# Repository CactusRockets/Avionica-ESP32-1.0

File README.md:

A aviônica embarcada foi prototipada e projetada através do software Eagle. Esse projeto inclui as dimensões da placa (PCB), a inclusão dos componentes da aviônica, as relações entre elas e o fornecimento de energia.

Dimensões da placa: 5,6 cm x 12,0 cm

Os materiais incluídos no projeto são:

- 1x PCB
- 1x ESP32 LoRa heltec (V2) + Antena
- 1x MPU6050
- 1X BMP280
- 2x JST de dois pinos (macho e fêmea) (2.54mm)
- 1x Conector microUSB
- 1x Switch (ss12f44g4)
- 1x Módulo SD + Cartão SD
- 1x Pino (PINHD 1X1)
- 2x Baterias de lítio (18650) (3.7V cada)
- 1x Suporte para duas baterias 18650
- Fios de ligação das baterias com o sistema

As trilhas da conexão entre os circuitos foram trilhas de 1mm de largura. A prototipação inclui uma chave de conexão que liga o JST (que se conecta a bateria) ao restante do circuito, para que possa ser feito um acionamento elétrico manual do sistema. Além desses componentes básicos, o projeto da placa inclui também 4x rebites de 2,7mm nas extremidades para fixação da placa.

O CAD está disponível no google Drive da Cactus.

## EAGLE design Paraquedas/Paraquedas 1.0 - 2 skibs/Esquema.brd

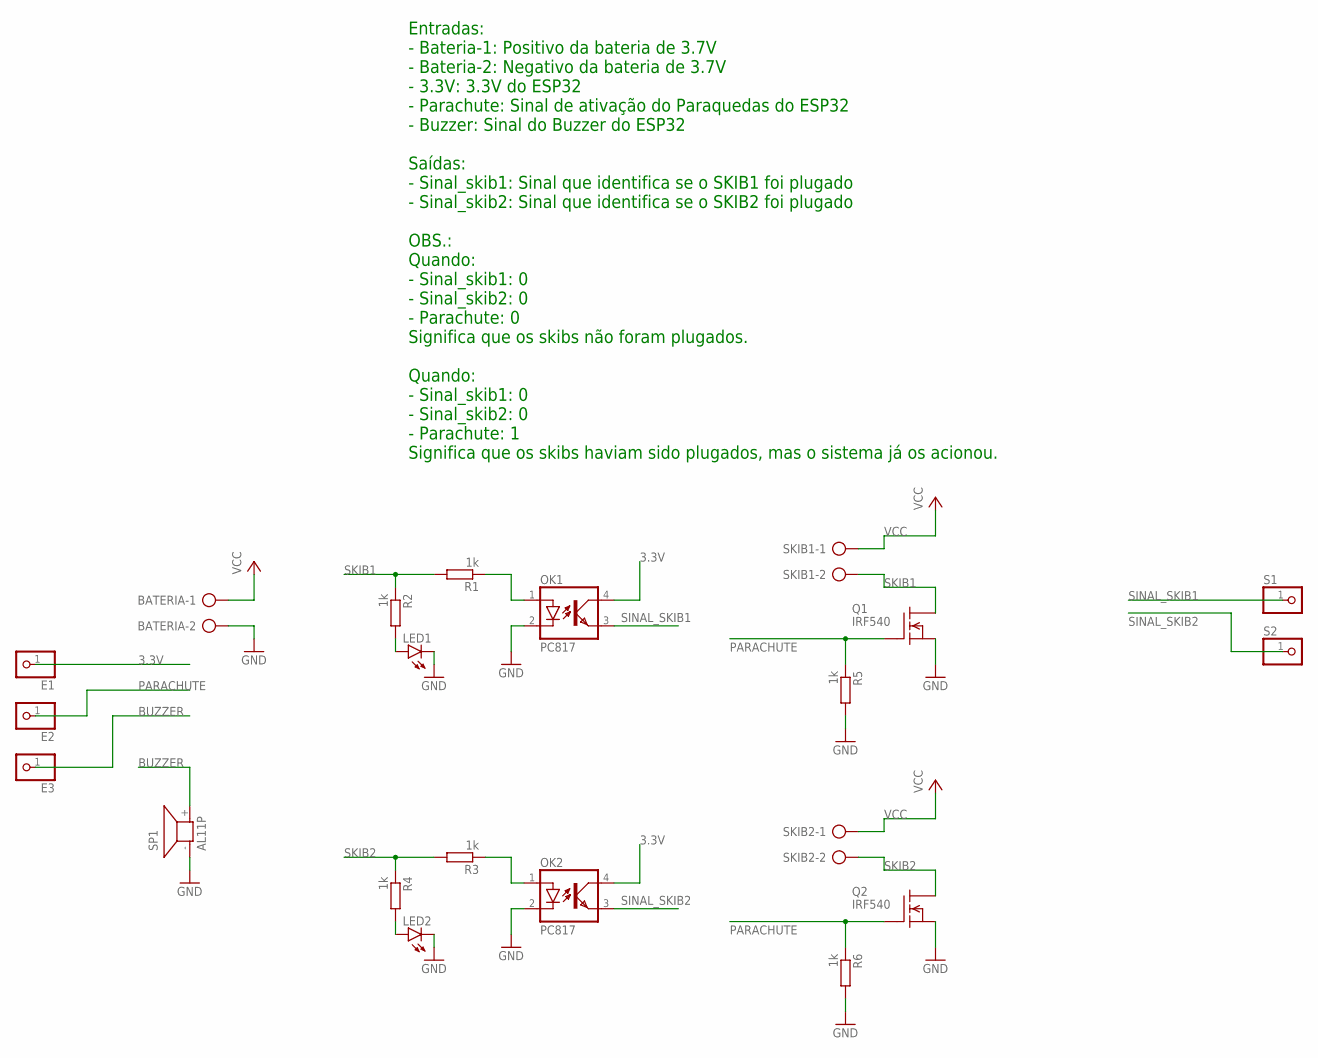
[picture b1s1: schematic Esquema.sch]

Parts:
BATERIA: AK500/2-H
E1, E2, E3: PINHD-1X1; 1X01
LED1, LED2: LED5MM
OK1, OK2: PC817; DIL04
Q1, Q2: IRF540; TO220
R1, R2, R3, R4, R5, R6: 1k; 0207/10
S1, S2: PINHD-1X1; 1X01
SKIB1, SKIB2: AK500/2-H
SP1: AL11P

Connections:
3.3V: E1.1, OK1.4 (COL), OK2.4 (COL)
BUZZER: E3.1, SP1.+ (2)
GND: BATERIA.2, LED1.K (C), LED2.K (C), OK1.2 (C), OK2.2 (C), Q1.3 (S), Q2.3 (S), R5.2, R6.2, SP1.- (1)
unnamed: OK1.1 (A), R1.1
unnamed: OK2.1 (A), R3.1
unnamed: LED2.A, R4.2
unnamed: LED1.A, R2.2
PARACHUTE: E2.1, Q1.1 (G), Q2.1 (G), R5.1, R6.1
SINAL_SKIB1: OK1.3 (EMIT), S1.1
SINAL_SKIB2: OK2.3 (EMIT), S2.1
SKIB1: Q1.2 (D), R1.2, R2.1, SKIB1.2
SKIB2: Q2.2 (D), R3.2, R4.1, SKIB2.2
VCC: BATERIA.1, SKIB1.1, SKIB2.1

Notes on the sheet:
Entradas: - Bateria-1: Positivo da bateria de 3.7V - Bateria-2: Negativo da bateria de 3.7V - 3.3V: 3.3V do ESP32 - Parachute: Sinal de ativação do Paraquedas do ESP32 - Buzzer: Sinal do Buzzer do ESP32 Saídas: - Sinal_skib1: Sinal que identifica se o SKIB1 foi plugado - Sinal_skib2: Sinal que iden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

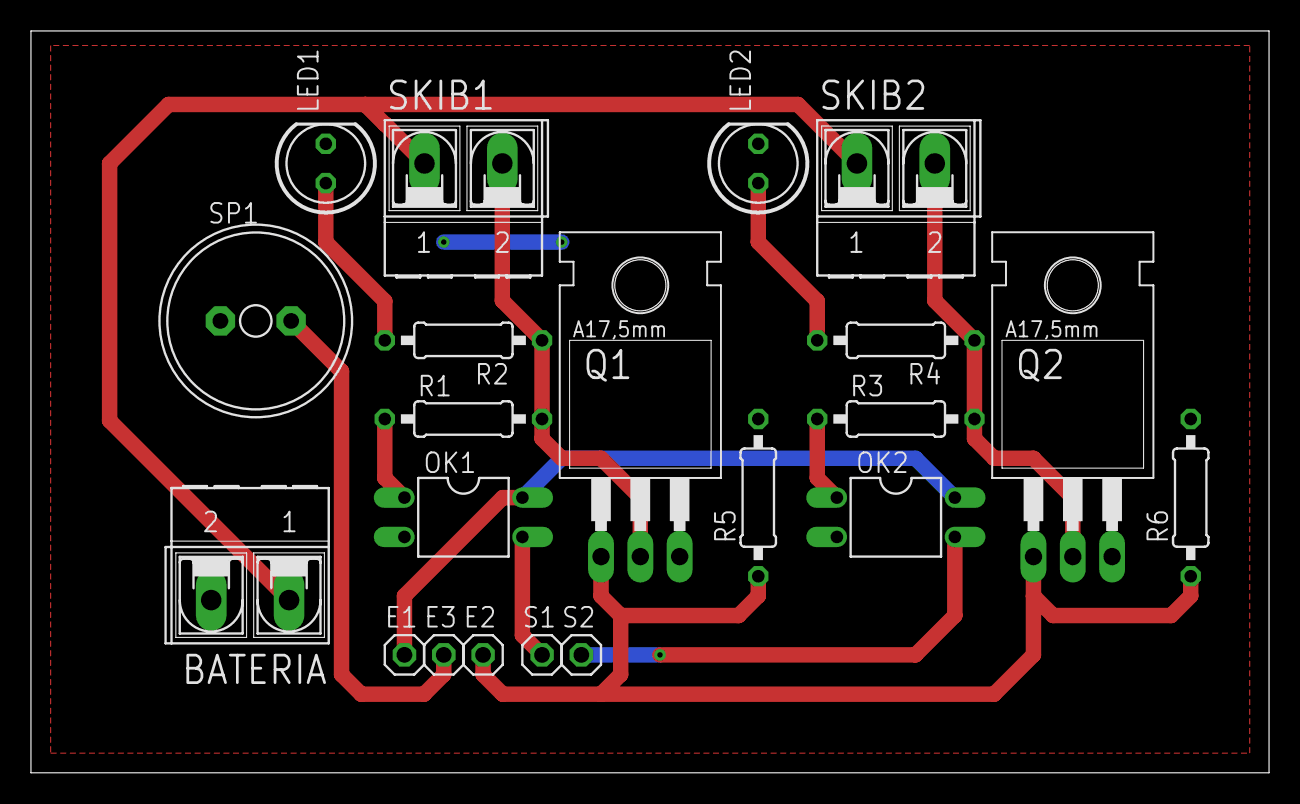
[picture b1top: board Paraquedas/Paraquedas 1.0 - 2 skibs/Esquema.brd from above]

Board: 2 copper layers, 80.0 x 47.9 mm, 21 parts (0 on the bottom side), 13 nets.

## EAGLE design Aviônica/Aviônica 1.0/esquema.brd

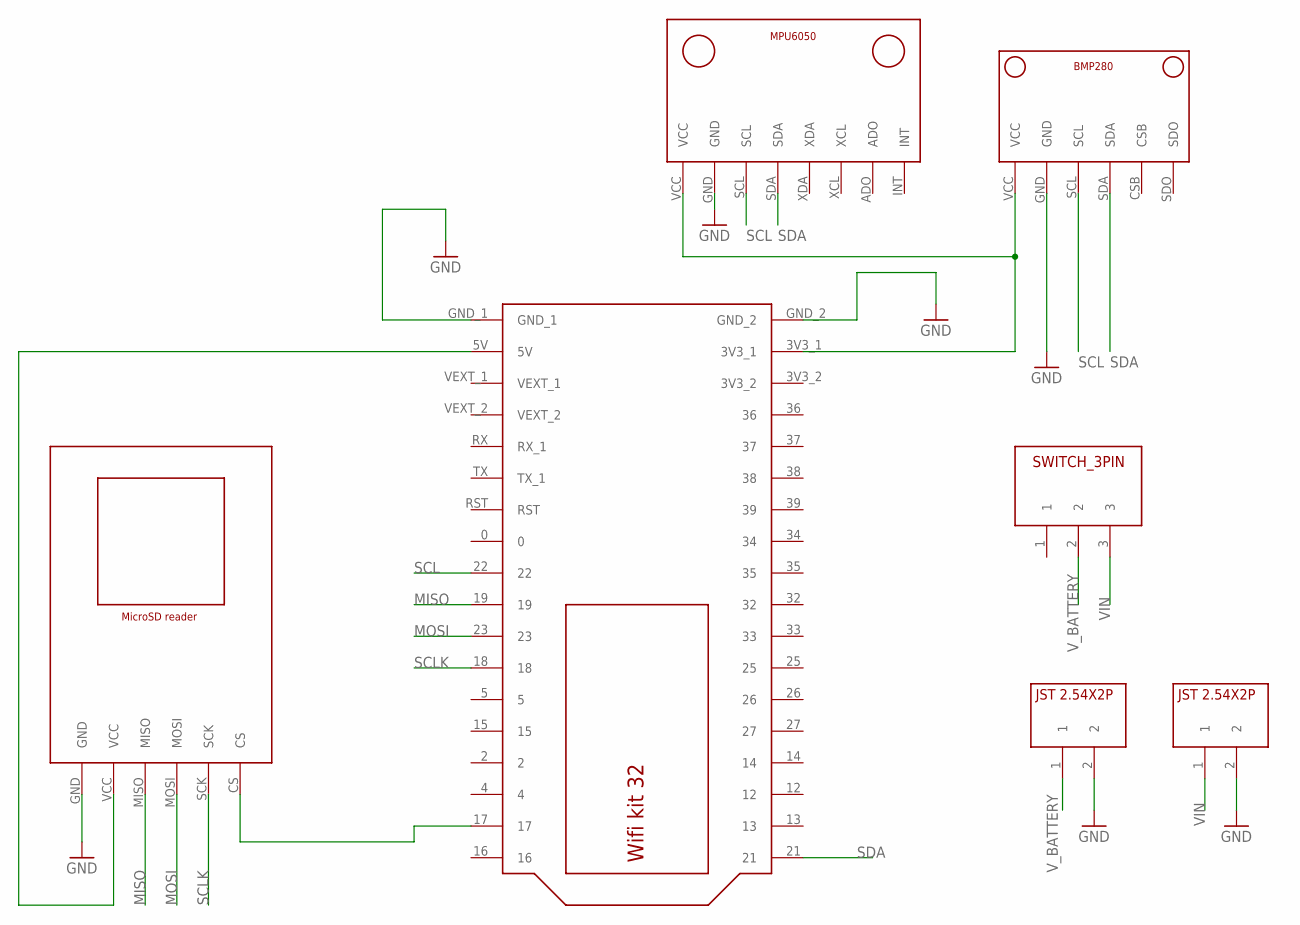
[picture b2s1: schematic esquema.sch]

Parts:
U$1: BMP280V1; BMP280_FOOTPRINT
U$2: MICROSD_READER; MICROSD_READER_FOOTPRINT
U$3: MPU6050V1; MPU6050_FOOTPRINT
U$4: WIFI_KIT32
U$5, U$7: JST2.54X2P; JST2.54X2P_FOOTPRINT
U$6: SWITCH_3PIN

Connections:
GND: U$1.GND, U$2.GND, U$3.GND, U$4.GND_1, U$4.GND_2, U$5.2, U$7.2
MISO: U$2.MISO, U$4.19
MOSI: U$2.MOSI, U$4.23
unnamed: U$2.CS, U$4.17
unnamed: U$1.VCC, U$3.VCC, U$4.3V3_1
unnamed: U$2.VCC, U$4.5V
SCL: U$1.SCL, U$3.SCL, U$4.22
SCLK: U$2.SCK, U$4.18
SDA: U$1.SDA, U$3.SDA, U$4.21
VIN: U$6.3, U$7.1
V_BATTERY: U$5.1, U$6.2

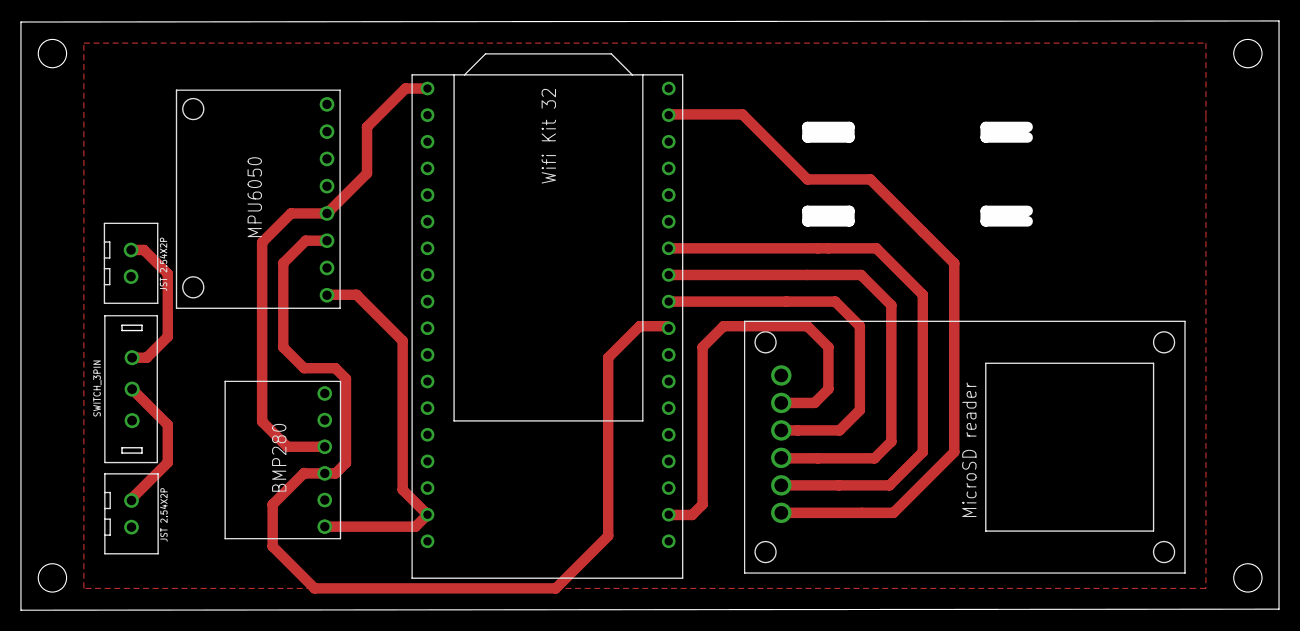
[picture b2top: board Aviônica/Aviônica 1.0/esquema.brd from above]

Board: 2 copper layers, 120.0 x 56.2 mm, 7 parts (0 on the bottom side), 11 nets.

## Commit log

2023-03-13 Atualizando
2023-03-22 Placa do paraquedas
2023-04-05 Atualização
2023-07-30 Message
